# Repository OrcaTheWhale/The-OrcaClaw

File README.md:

# The-OrcaClaw
Resembling (sort of) Victor's Hexclaw from League of Legends/Arcane, the OrcaClaw is a powerful(weak) arm that can be controlled remotely, and has the ability to grab and point using a laser!

This is my first ever project outside of tinkering with a breadboard and sensors. I've never modeled, made a pcb, or know a lot about assembly(hardware components, screw types). However, after a lot of work and hours done, I was able to learn a lot, and also was able to produce this project, the OrcaClaw!

**What makes this unique**: You will never see this in the real world(cause it's kinda useless), that's just how unique it is! Resembling a Hexclaw and an Orca, the OrcaClaw is able to be able to grab _some_ items in your daily life! Whether you need to hold on to an empty soda can(for some reason), or claw menacingly at someone you don't like, the OrcaClaw, _in addition_, allows you to point at things using it's built in laser! Just like the Hexclaw, it's dangerous(if you shine it in someone's eyes, don't do that), and can ward off people who don't like light(like vampires)!

**Why I made this project**: Originally, I was going to create just a robot arm that is able to write something, with remote capabilities, like either being remote controlled or master-slave. The reason the idea pivoted was because after joining the Fallout kickoff call, I was more inspired to create something not so boring and unoriginal. An arm seemed like a perfect guide in my opinion; I will be able to make something move(neurons firing!), and learn modeling, creating PCB's, and wireless communication. I was still able to learn everything; but now the idea is much cooler! 

Here is a list of things I learned from this project:

**Modeling**

**PCB Creation**

Assembly: 
- Different screw uses (M3 Machine Vs Thread forming, M2.6 for circuit boards)
- Onshape Assembly
- Claw Machine/Linkage style claw mechanism
- Tolerances
  
Hardware:
- Voltage step-down (Buck Converter)
- Wary of current draw (Increasing wire thickness and AWG sizes)
- Wary of current draw x2 (Capacitors for MG996R Servos)
- MOSFET gate

And more!

Here is a list of _problems_ I ran into for this project:
- WHY IS EVERYTHING EXPENSIVE
- Batteries < $20 having the battery life of a potato
- One of the batteries I bought was fine then I realized later the turtle from the tortoise and the hare race was the one delivering the product
- Buying components irl to accomodate in the design, and then realising there were cheaper options so now I have to buy those ones to stick to the BOM and source material
- Errors in OnShape
- Extrude? Hello? It's a closed area?
- Had to restart early on, not too bad though
- Screws not screwing (There's two types of screws, machine screws and thread-forming???)
- Tolerances not tolerating
- Logic errors
- Having to sacrifice a lot of rotation degrees
- Chance of the first MG996R not being able to hold up
- Trying to install the XIAO footprint (wth is git submodules and somethingEDA)
- Trying to upload the PCB to JLCPCB (literally only the holes appeared for some reason)
- AliExpress shipping lowkey being the product
- AliExpress being a master of manipulation (they removed a $20 off deal the moment I hit buy)
- One of the only good laser modules is $20 (wth)
- Slack, Fallout issues (why is fallout using a slack I never technically created?)
- Doing research at night, thinking it'd only take me a few minutes but taking me 1-2 hours I could've tracked
- Github uploading the individual files instead of the folder
- Realizing I had put two buttons on the controller pcb when I need 3 (control, claw, and laser)
- Zine page looking ahh
- Being ghosted in slack :sob: not that much tho shout out Tirthak and the gang
- AAAAAHHH

OrcaClaw 3D Model:

OrcaController 3D Model:

OrcaClaw PCB:

OrcaClaw Controller PCB:

**Wiring Diagram / Schematic:**

OrcaClaw Schematic:

The OrcaClaw controller schematic is just the PCB schematic with a extra battery:

**How to use:** 

Attach arm and backpack straps with the clips onto the backplate. Wear it like a backpack. Congratulations! The OrcaClaw is now mounted on your back! 

On the controller, there is two buttons. One of them allow for movement control. By pressing it down and moving your arm accordingly, the accelerometer will translate that movement into the servo movement. If you move your arm left or right, it'll follow left or right. If you move your arm up or down, it'll follow your arm movement. To close/open the claw, turn the controller on the Z axis.

The other button activates the laser. Please be careful and don't shine it in someone's eyes, it will be harmful.

**Guide:**
Once accepted, a more in depth guide will be posted. For now:

Follow OnShape document for where parts go! Almost all of the parts are unique in some way; so it won't be too hard to distinguish parts in assembly.
The longer M3 thread-forming screws (4 of them) goes from the backplate --> the arm segment connecting to it. 
Everything else uses the majority M3 thread-forming screws listed in the BOM.
The components relating to the claw use the M3 machine screws with nuts to keep them in place. Do not tighten nuts to the fullest, let parts be able to rotate.

Mount components to their respective places first, and then connect the arm pieces together.
Battery: There will be a rectangle piece which you slide in after putting the battery in its case, to keep it in place.
Same with the laser, but it will be a round piece.

The PCB's and other boards use the M2.6 screws through the mounting holes.

The absolute MESS of a cad(LISTEN. THIS THE FIRST TIME I'M ACTUALLY DOING MODELING. I DIDN'T REALIZE IT WOULD LOOK THIS UNORGANIZED. PLEASE SPARE ME):
https://cad.onshape.com/documents/d7ad806e815c1aad37a0e64a/w/e4d9f00fe60cfe8595f9785c/e/b1601408fc0aed2b47a9de74?renderMode=0&uiState=69e82076497156923c10f2e7 

You may find the **BOM** here: https://github.com/OrcaTheWhale/The-OrcaClaw/blob/d58308c58e4bb3730a3b75af7c206a2e41ff7d3b/Bill%20of%20Materials.csv

You may find the **PCB Components Guide** here: https://github.com/OrcaTheWhale/The-OrcaClaw/blob/main/PCBFiles/PCB%20Components%20Guide.csv

**HEADS UP!** The BOM assumes you have a soldering iron. The prices are in CAD(Canadian money, not modeling software you nerds), and shipping prices will vary from region.
The printing legion shipping cost also may vary.

Buck Converter MAY NOT BE ACCURATE! Listing says 2 different dimensions; when I recieve it I will update the model. It also may be M3 mounting holes, and M2.6. However, the parts in the BOM have enough thread-forming screws to use M3 instead. Warning: Pilot hole will be a tight fit.

The firmware is also set in platformio! If you are using Arduino IDE, please feel free to do so.

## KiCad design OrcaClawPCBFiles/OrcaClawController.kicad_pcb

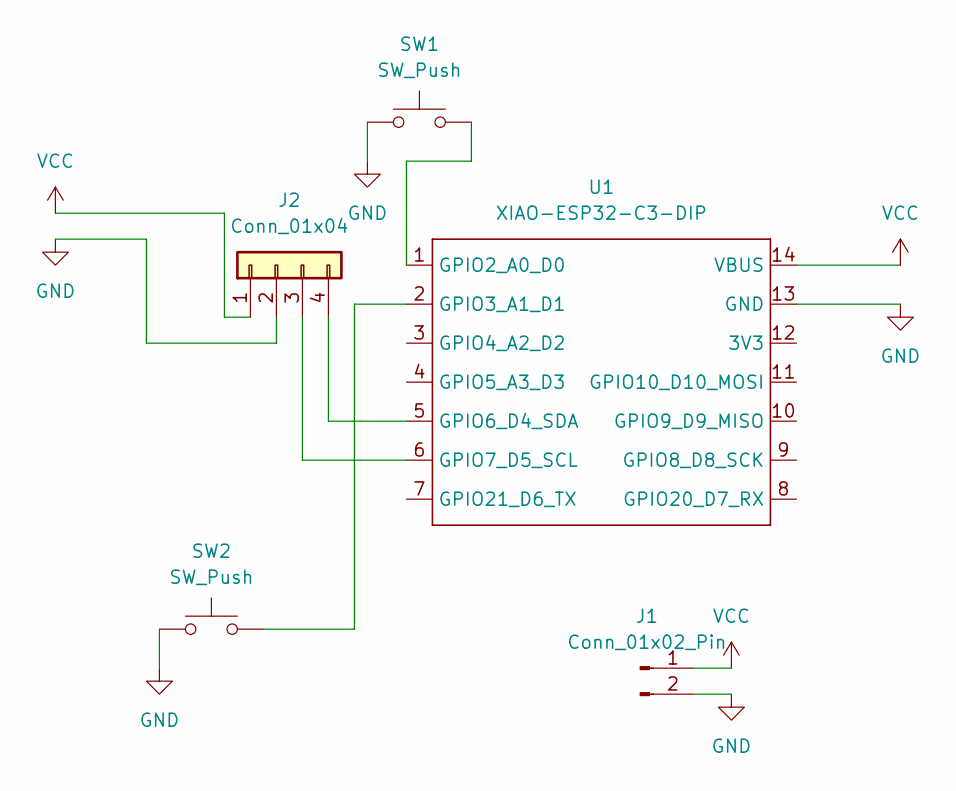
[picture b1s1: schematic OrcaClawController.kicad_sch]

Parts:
J1: Conn_01x02_Pin; PinHeader_1x02_P2.00mm_Vertical
J2: Conn_01x04; PinHeader_1x04_P2.54mm_Vertical
SW1, SW2: SW_Push; SW_PUSH_6mm
U1: XIAO-ESP32-C3-DIP

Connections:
GND: J1.2, J2.2, SW1.1, SW2.1, U1.13 (GND)
unnamed: J2.3, U1.6 (GPIO7_D5_SCL)
unnamed: J2.4, U1.5 (GPIO6_D4_SDA)
unnamed: SW1.2, U1.1 (GPIO2_A0_D0)
unnamed: SW2.2, U1.2 (GPIO3_A1_D1)
VCC: J1.1, J2.1, U1.14 (VBUS)

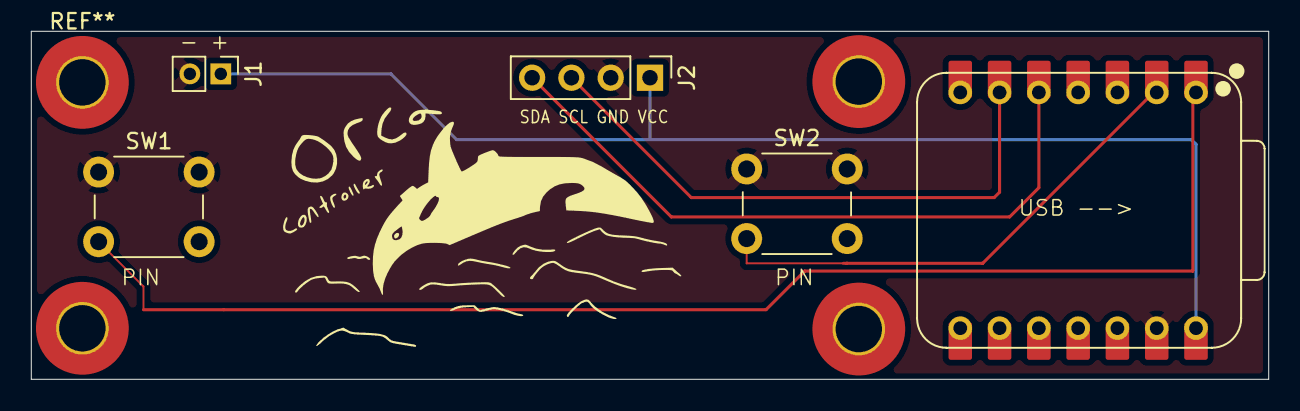
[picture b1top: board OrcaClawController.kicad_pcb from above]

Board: 4 copper layers, 80.0 x 22.5 mm, 5 parts (0 on the bottom side), 6 nets.

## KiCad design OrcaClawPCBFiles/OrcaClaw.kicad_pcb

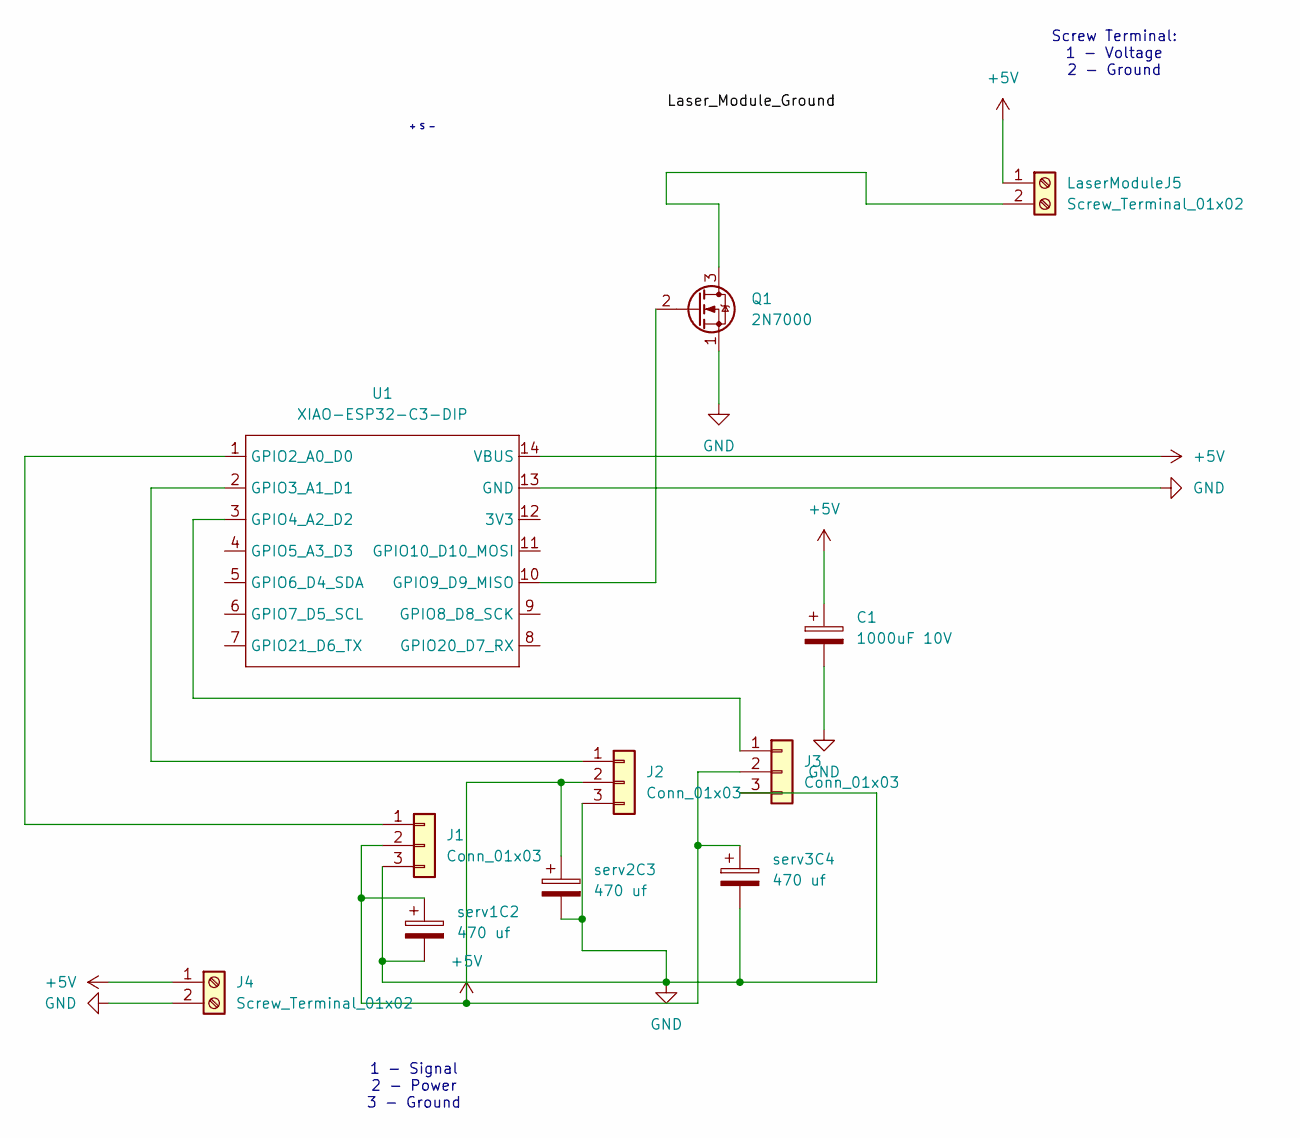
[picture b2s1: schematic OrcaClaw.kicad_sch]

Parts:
C1: 1000uF 10V; CP_Radial_D10.0mm_P5.00mm
J1, J2, J3: Conn_01x03; PinHeader_1x03_P2.54mm_Vertical
J4: Screw_Terminal_01x02; TerminalBlock_Phoenix_MKDS-1,5-2-5.08_1x02_P5.08mm_Horizont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
LaserModuleJ5: Screw_Terminal_01x02; TerminalBlock_Phoenix_MKDS-1,5-2-5.08_1x02_P5.08mm_Horizont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
Q1: 2N7000; TO-92_Inline
U1: XIAO-ESP32-C3-DIP
serv1C2, serv2C3, serv3C4: 470 uf; CP_Radial_D8.0mm_P3.50mm

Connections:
+5V: C1.1, J1.2, J2.2, J3.2, J4.1, LaserModuleJ5.1, U1.14 (VBUS), serv1C2.1, serv2C3.1, serv3C4.1
GND: C1.2, J1.3, J2.3, J3.3, J4.2, Q1.1 (S), U1.13 (GND), serv1C2.2, serv2C3.2, serv3C4.2
unnamed: J1.1, U1.1 (GPIO2_A0_D0)
unnamed: J2.1, U1.2 (GPIO3_A1_D1)
unnamed: J3.1, U1.3 (GPIO4_A2_D2)
unnamed: LaserModuleJ5.2, Q1.3 (D)
unnamed: Q1.2 (G), U1.10 (GPIO9_D9_MISO)

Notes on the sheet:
1 - Signal 2 - Power 3 - Ground
+ S -
Screw Terminal: 1 - Voltage 2 - Ground

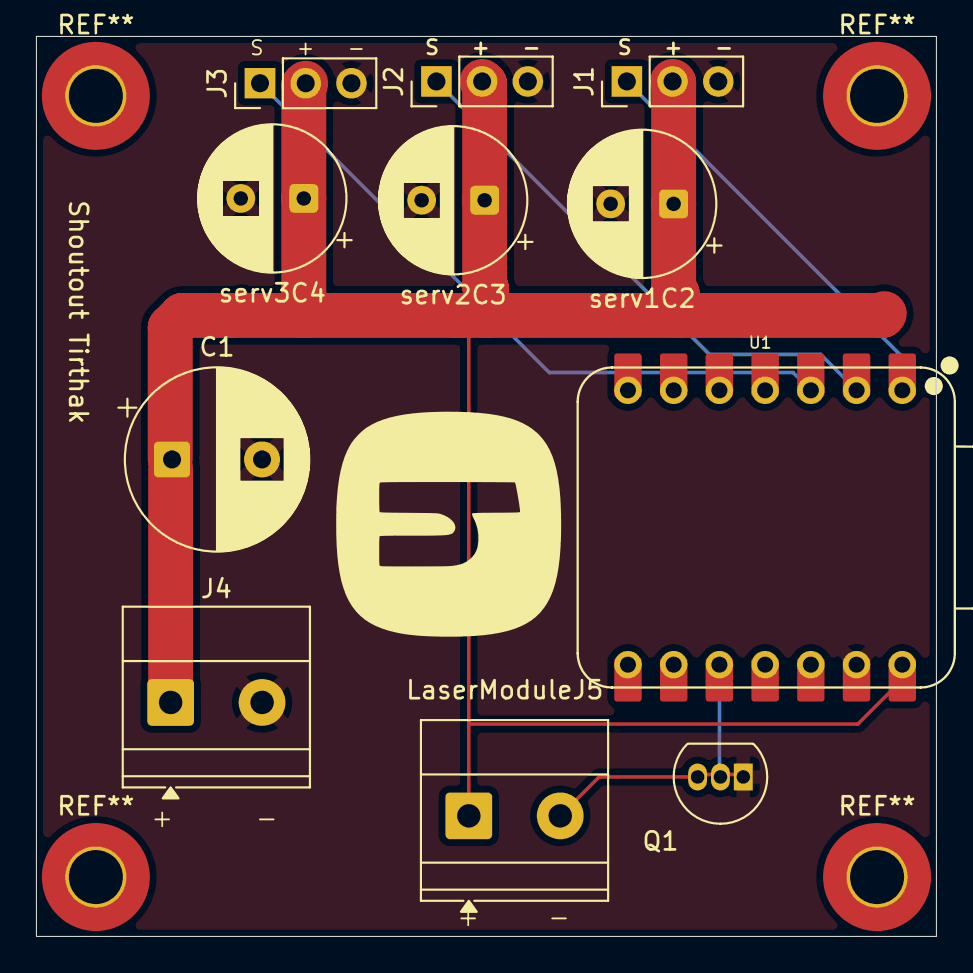
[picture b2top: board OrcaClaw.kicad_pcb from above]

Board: 4 copper layers, 50.0 x 50.0 mm, 12 parts (0 on the bottom side), 7 nets.

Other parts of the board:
.: LOGO

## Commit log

2026-04-21 Create Docs
